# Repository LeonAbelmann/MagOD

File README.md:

# MagOD
Magnetic Optical Density meter
Tijmen Hageman, Jordi Hendrix, Hans Keizer, Marcel Welleweerd, Dave
van As, Ruthvik Bandaru, Rob Krawinkel, Leon Abelmann.

KIST Europe, University of Twente

## Other sources
Next to software, also the source codes to create hardware are
available here, as well as :

- Measurement head design, 3D print file (OpenSCAD, on [Thingiverse](https://www.thingiverse.com/thing:3122930) )
- Spice simulations, electronic diagrams, PCB layout (Spice, KiCad on
  [Dropbox](https://www.dropbox.com/sh/1dcai82byvd3hy0/AAA3AGXw0jbr9n2gzdcszufia))
- Laser cut pattern for housing electronics (DXF, on [Dropbox](https://www.dropbox.com/sh/1dcai82byvd3hy0/AAA3AGXw0jbr9n2gzdcszufia))

## Specifications
- Up to 800 samples per second, allows precise analysis of the rotation speed of magnetic bacteria
- Three-dimensional quasi-Helmholtz configuration, with fields up to 5 mT 
- Three color LED: red: 645 nm, 1000 mcd, green: 520 nm, 1700 mcd and blue 460 nm, 500 mcd
- Power supply with current feedback to compensate for coil heating, cut-off frequency 200 Hz
- Large area photodiode (sensitivity 0.5 mlx, with green LED theoretical max OD range of 5.8)
- Integrated pre-amplifier, SNR 83 dB (max OD range 4.0).
- Dedicated 16-bit ADS1115 DA converter
- Integrated temperature sensor
- Reference light detector
- Scattered light detector
- Fully programmable (ESP32 using Arduino IDE), open source
- User friendly spreadsheet recipe definition (csv format), with software to validate correctness
- Data collection on SD card, accessible by ftp over Wifi

## Additional info
- Marcel Welleweerd *and colleagues* (2022) ["An open-source automated magnetic optical density meter for analysis of suspensions of magnetic cells and particles"](https://doi.org/10.1063/5.0098008) Review of Scientific Instruments Vol 93, Issue 9, 094101. The manuscript can be found on [ArXiv](https://arxiv.org/abs/2106.07466)
- Chapter 8 in [Thesis](https://research.utwente.nl/en/publications/observing-magnetic-objects-in-fluids) Tijmen Hageman.
- [Presentation](https://youtu.be/TwwIsPg0qnI) by Leon Abelmann at Intermag2021

## How to join
Send mail to Leon (l.abelmann@tudelft.nl) if you are interested, all skills are welcome.

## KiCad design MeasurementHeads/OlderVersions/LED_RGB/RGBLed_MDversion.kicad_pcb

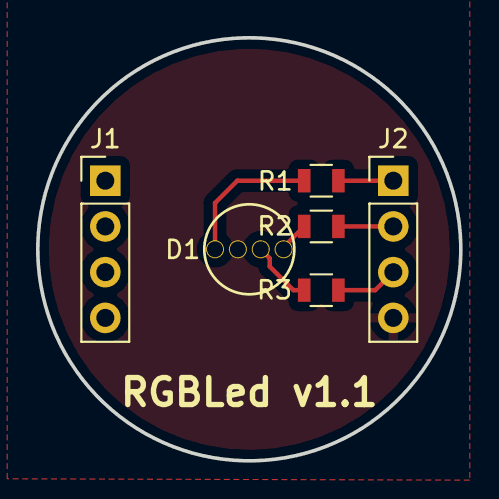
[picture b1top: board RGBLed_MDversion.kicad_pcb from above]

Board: 2 copper layers, 23.5 x 23.5 mm, 6 parts (0 on the bottom side), 7 nets.

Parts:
D1: LED_RABG; L-154A4SUREQBFZGEW
J1, J2: Conn_01x04; Socket_Strip_Straight_1x04_Pitch2.54mm
R1, R2, R3: R; R_0805

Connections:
+5V: D1.2, J2.4
/B: J2.3, R3.2
/G: J2.2, R2.2
/R: J2.1, R1.2
unnamed: D1.1, R1.1
unnamed: D1.3, R3.1
unnamed: D1.4, R2.1

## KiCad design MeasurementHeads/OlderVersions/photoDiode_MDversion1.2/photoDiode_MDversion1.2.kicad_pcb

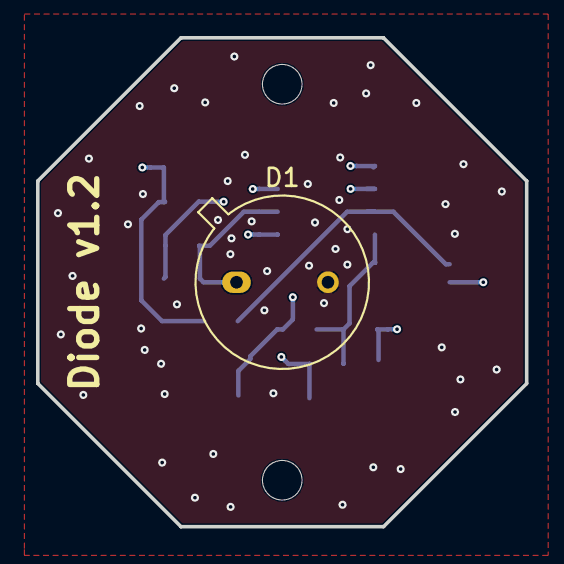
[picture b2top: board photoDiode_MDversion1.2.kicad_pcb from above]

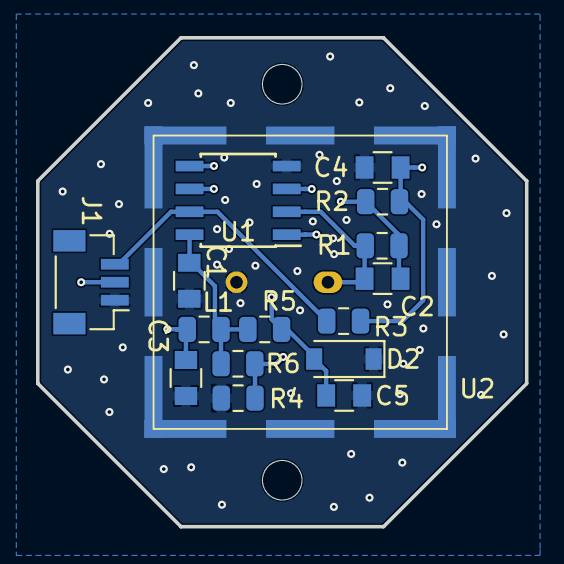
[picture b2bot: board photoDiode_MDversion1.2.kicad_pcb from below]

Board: 4 copper layers, 27.2 x 27.2 mm, 17 parts (16 on the bottom side), 9 nets.

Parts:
C1: 0.1uF; C_0805
C2, C5: C; C_0805
C3: 1.5uF; C_0805
C4: 47uF; C_0805
D1: BPW21; TO-5-2_Window
D2: D; D_SOD-123
J1: Conn_01x03; Molex_Pico-Clasp_501331-0307_1x03-1MP_P1.00mm_Vertical
L1: Ferrite_Bead; L_0805_2012Metric
R1, R3, R4, R5, R6: R; R_0805_2012Metric
R2: 3; R_0805_2012Metric
U1: Opamp_Dual_Generic; SOIC-8_3.9x4.9mm_Pitch1.27mm
U2: EMIshield; Laird-BMI-S-202-F

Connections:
+5V: C3.2, J1.2, L1.1
/A: J1.3, R3.2, U1.7
/Vdd: C1.1, L1.2, R5.2, R6.2, U1.8
GND: C1.2, C3.1, C4.2, C5.2, D1.2, D2.1, J1.1, R4.1, U1.4, U2.1
unnamed: C2.1, R1.2, R2.1, U1.1
unnamed: C2.2, D1.1, R1.1, U1.2
unnamed: C4.1, R2.2, R3.1, U1.6
unnamed: C5.1, D2.2, R5.1, U1.3
unnamed: R4.2, R6.1, U1.5

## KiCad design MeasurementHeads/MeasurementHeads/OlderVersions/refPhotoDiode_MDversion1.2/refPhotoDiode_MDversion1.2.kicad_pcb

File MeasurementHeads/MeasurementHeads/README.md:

# Measurement head electronics
photoDiode : photodetector
refPhotoDiode: board to holde RBG led/LED-mono module and reference photodiode
RGBLed: RGB Led module
LED_mono: Monochrome led module

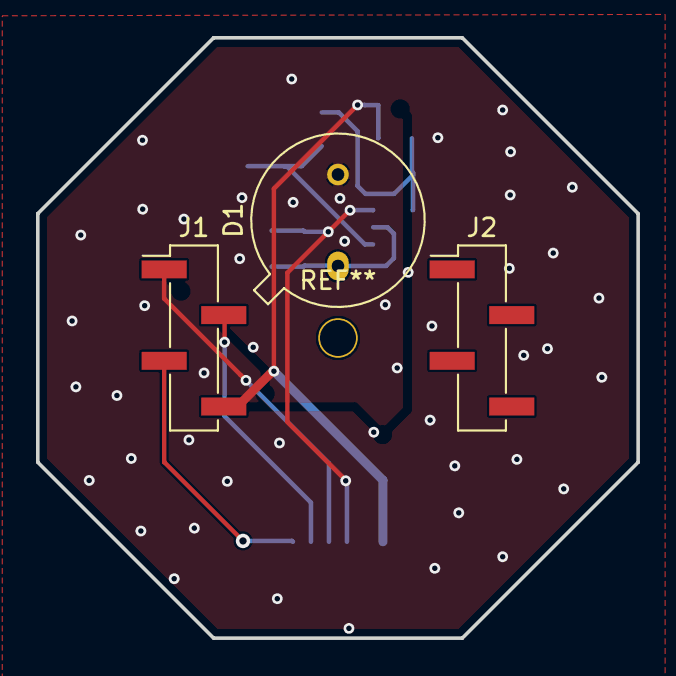
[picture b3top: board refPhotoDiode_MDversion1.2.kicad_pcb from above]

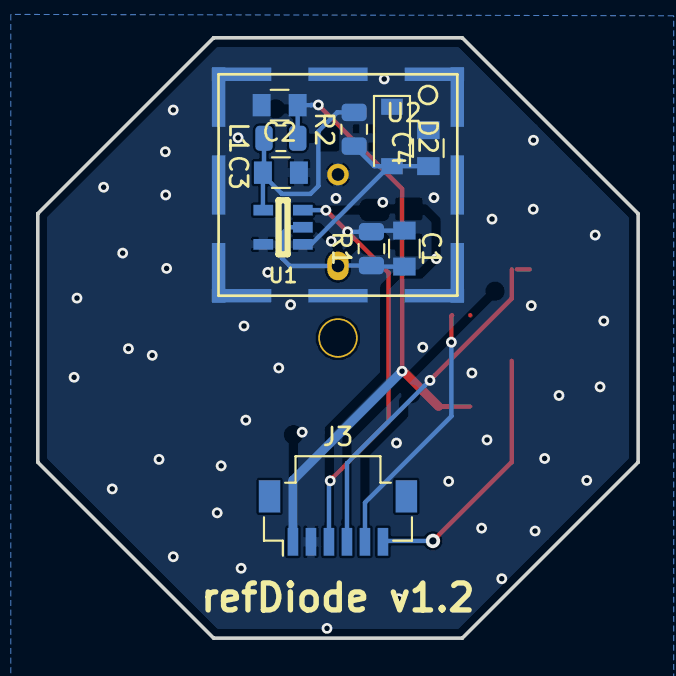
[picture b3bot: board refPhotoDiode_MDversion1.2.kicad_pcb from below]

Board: 2 copper layers, 33.4 x 33.4 mm, 14 parts (11 on the bottom side), 9 nets.

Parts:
C1, C4: C; C_0805
C2: 1.5uF; C_0805
C3: 0.1uF; C_0805
D1: BPW21; TO-5-2_Window
D2: D; D_SOD-123
J1, J2: Conn_01x04; PinHeader_1x04_P2.54mm_Vertical_SMD_Pin1Left
J3: Conn_01x06; Molex_Pico-Clasp_501331-0607_1x06-1MP_P1.00mm_Vertical
L1: Ferrite_Bead; L_0805_2012Metric
R1, R2: R; R_0805_2012Metric
U1: OPAMP; SOT-23-5
U2: EMIshield; Wurth-3610213126S-EMIshield-13.26x12.3mm

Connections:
+5V: C2.1, J1.4, J3.1, L1.1
/A: C1.1, J3.3, R1.2, U1.3
/B: J1.3, J3.6
/G: J1.2, J3.5
/R: J1.1, J3.4
/V: C3.1, L1.2, R2.2, U1.4
GND: C2.2, C3.2, C4.2, D1.2, D2.1, J3.2, U1.5, U2.1
unnamed: C1.2, D1.1, R1.1, U1.2
unnamed: C4.1, D2.2, R2.1, U1.1

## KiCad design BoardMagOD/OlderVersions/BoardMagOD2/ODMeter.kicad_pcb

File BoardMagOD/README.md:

# Measurement Board
Electronic design of measurement board

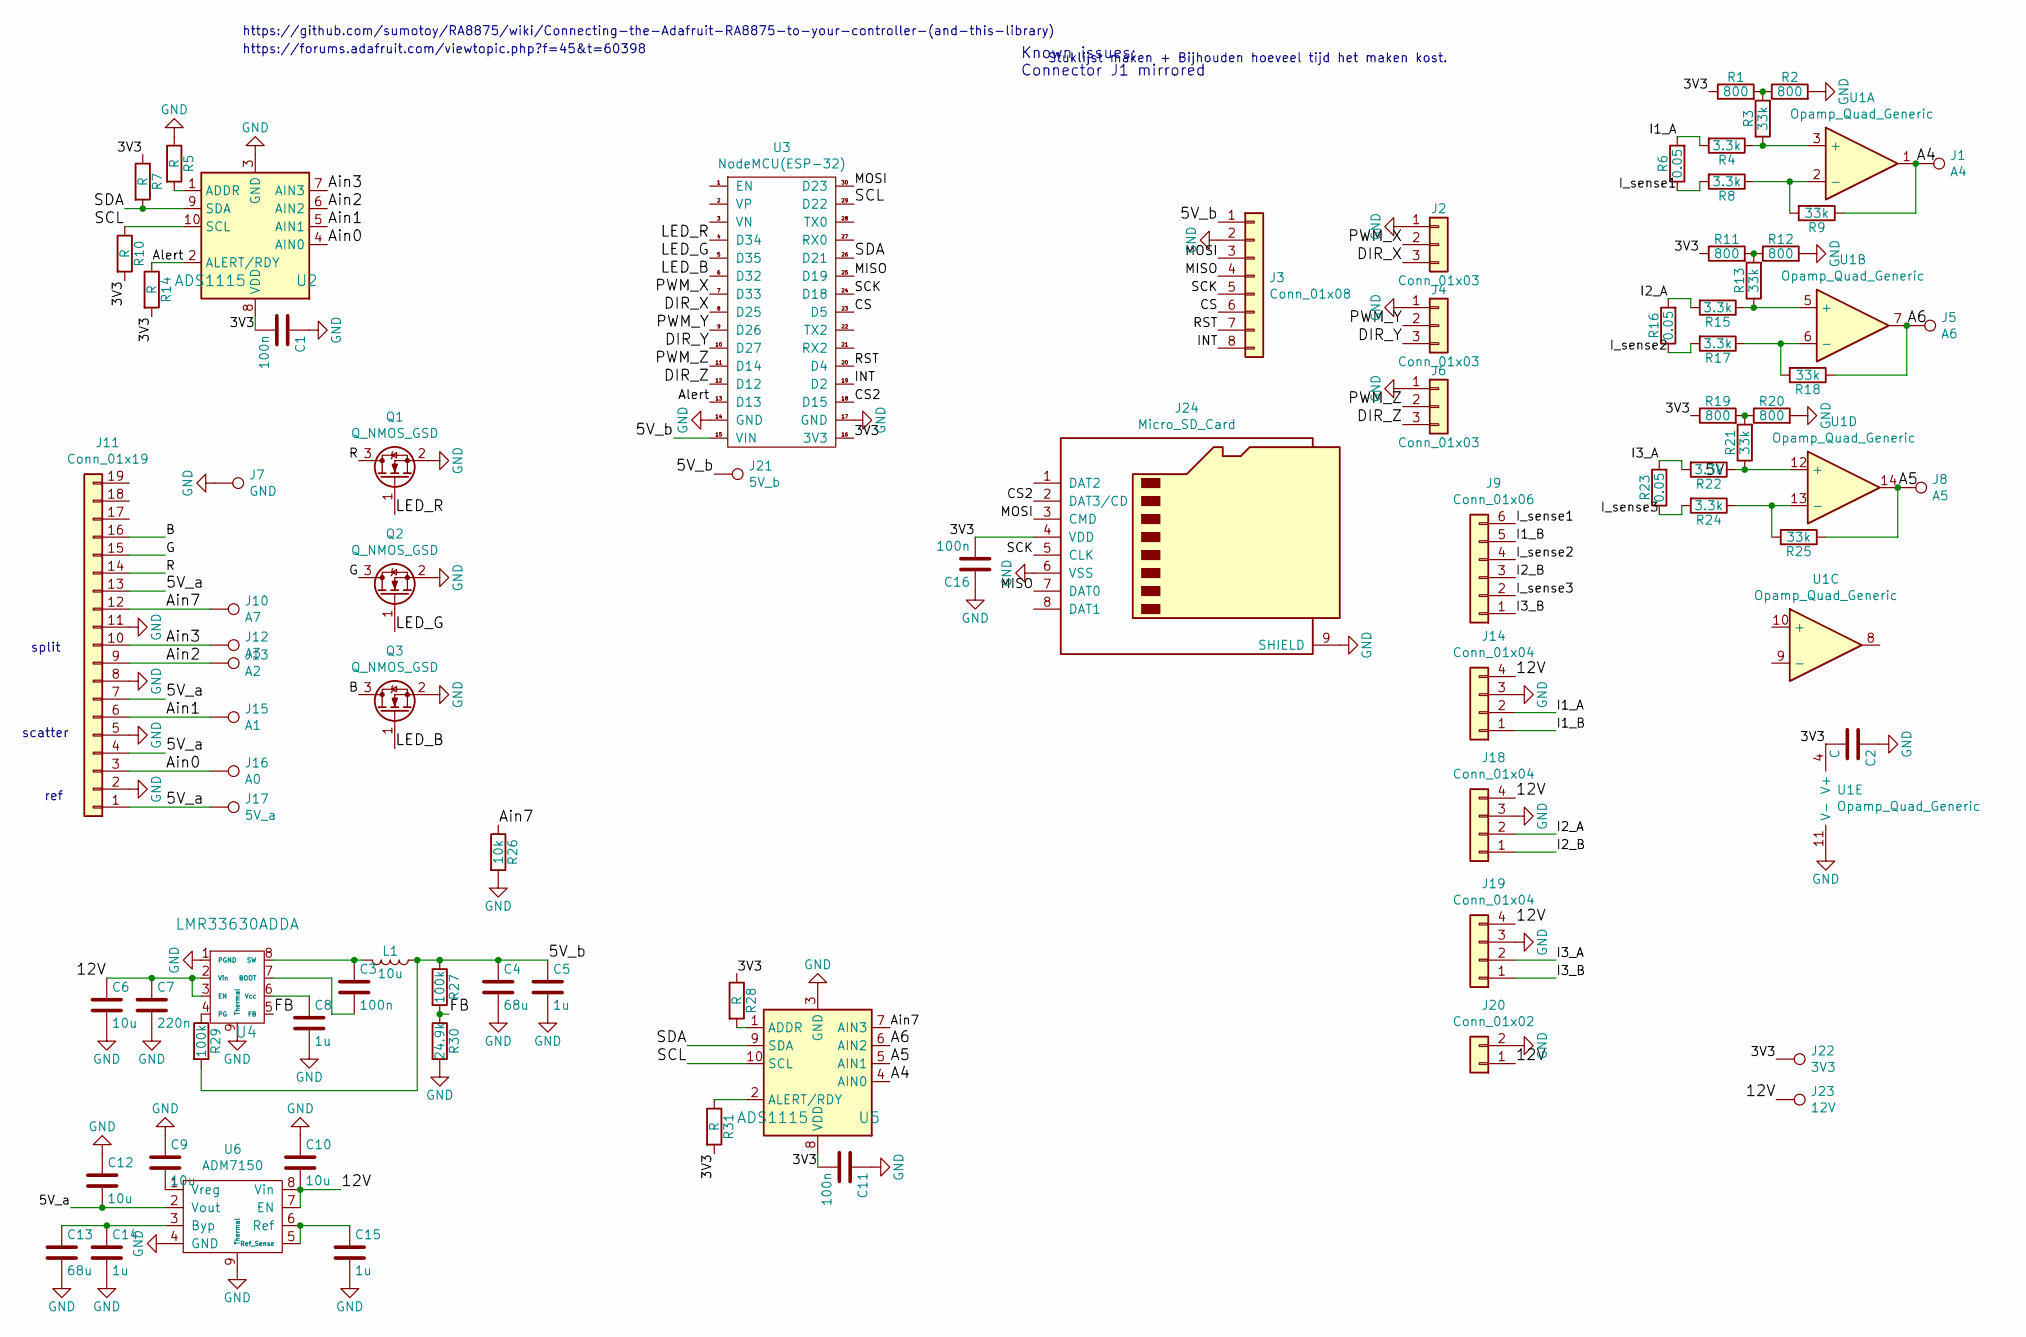
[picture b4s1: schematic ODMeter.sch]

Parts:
C1, C3, C11, C16: 100n; C_0805
C2: C; C_0805
C4, C13: 68u; CP_Tantalum_Case-D_EIA-7343-31_Hand
C5: 1u; C_0805
C6, C9, C10, C12: 10u; C_1210
C7: 220n; C_0805
C8, C14, C15: 1u; C_0603
J1: A4; TestPoint-Harwin-S2761-46R
J2, J4, J6: Conn_01x03; Pin_Header_Straight_1x03_Pitch2.54mm
J3: Conn_01x08; Pin_Header_Straight_1x08_Pitch2.54mm
J5: A6; TestPoint-Harwin-S2761-46R
J7: GND; TestPoint-Harwin-S2761-46R
J8: A5; TestPoint-Harwin-S2761-46R
J9: Conn_01x06; KK41791_straight1x6
J10: A7; TestPoint-Harwin-S2761-46R
J11: Conn_01x19; HDMI-RightAngle-47151-1051
J12: A3; TestPoint-Harwin-S2761-46R
J13: A2; TestPoint-Harwin-S2761-46R
J14, J18, J19: Conn_01x04; KK41791_straight1x4
J15: A1; TestPoint-Harwin-S2761-46R
J16: A0; TestPoint-Harwin-S2761-46R
J17: 5V_a; TestPoint-Harwin-S2761-46R
J20: Conn_01x02; KK396RPC171813_Straight_1x2
J21: 5V_b; TestPoint-Harwin-S2761-46R
J22: 3V3; TestPoint-Harwin-S2761-46R
J23: 12V; TestPoint-Harwin-S2761-46R
J24: Micro_SD_Card; MicroSd_Wurth_693072010801
L1: 10u; ssr1260
Q1, Q2, Q3: Q_NMOS_GSD; SOT-23
R1, R2, R11, R12, R19, R20: 800; R_0805
R3, R9, R13, R18, R21, R25: 33k; R_0805
R4, R8, R15, R17, R22, R24: 3.3k; R_0805
R5, R7, R10, R14, R28, R31: R; R_0805
R6, R16, R23: 0.05; OAR3
R26: 10k; R_0805
R27, R29: 100k; R_0805
R30: 24.9k; R_0805
U1: Opamp_Quad_Generic; SOIC-14_3.9x8.7mm_P1.27mm
U2, U5: ADS1115; VSSOP-10_3.1x3.1mm_Pitch0.5mm
U3: NodeMCU(ESP-32)
U4: LMR33630ADDA; HSOIC-8
U6: ADM7150; HSOIC-8

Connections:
/3V3: C1.2, C2.2, C11.2, C16.2, J22.1, J24.4 (VDD), R1.1, R7.1, R10.2, R11.1, R14.2, R19.1, R28.1, R31.2, U1.4 (V+), U2.8 (VDD), U3.16 (3V3), U5.8 (VDD)
/5V_a: C12.2, J11.1, J11.4, J11.7, J11.13, J17.1, U6.2 (Vout)
/5V_b: C4.1, C5.1, J3.1, J21.1, L1.1, R27.1, R29.2, U3.15 (VIN)
/12V: C6.1, C7.1, C10.2, J14.4, J18.4, J19.4, J20.1, J23.1, U4.2 (Vin), U4.3 (EN), U6.7 (EN), U6.8 (Vin)
/A4: J1.1, R9.1, U1.1, U5.4 (AIN0)
/A5: J8.1, R25.1, U1.14, U5.5 (AIN1)
/A6: J5.1, R18.1, U1.7, U5.6 (AIN2)
/Ain0: J11.3, J16.1, U2.4 (AIN0)
/Ain1: J11.6, J15.1, U2.5 (AIN1)
/Ain2: J11.9, J13.1, U2.6 (AIN2)
/Ain3: J11.10, J12.1, U2.7 (AIN3)
/Ain7: J10.1, J11.12, R26.1, U5.7 (AIN3)
/Alert: R14.1, U2.2 (ALERT/RDY), U3.13 (D13)
/B: J11.16, Q3.3 (D)
/CS: J3.6, U3.23 (D5)
/CS2: J24.2 (DAT3/CD), U3.18 (D15)
/DIR_X: J2.3, U3.8 (D25)
/DIR_Y: J4.3, U3.10 (D27)
/DIR_Z: J6.3, U3.12 (D12)
/FB: R27.2, R30.1, U4.5 (FB)
/G: J11.15, Q2.3 (D)
/I1_A: J14.2, R4.2, R6.2
/I1_B: J9.5, J14.1
/I2_A: J18.2, R15.2, R16.2
/I2_B: J9.3, J18.1
/I3_A: J19.2, R22.2, R23.2
/I3_B: J9.1, J19.1
/INT: J3.8, U3.19 (D2)
/I_sense1: J9.6, R6.1, R8.2
/I_sense2: J9.4, R16.1, R17.2
/I_sense3: J9.2, R23.1, R24.2
/LED_B: Q3.1 (G), U3.6 (D32)
/LED_G: Q2.1 (G), U3.5 (D35)
/LED_R: Q1.1 (G), U3.4 (D34)
/MISO: J3.4, J24.7 (DAT0), U3.25 (D19)
/MOSI: J3.3, J24.3 (CMD), U3.30 (D23)
/PWM_X: J2.2, U3.7 (D33)
/PWM_Y: J4.2, U3.9 (D26)
/PWM_Z: J6.2, U3.11 (D14)
/R: J11.14, Q1.3 (D)
/RST: J3.7, U3.20 (D4)
/SCK: J3.5, J24.5 (CLK), U3.24 (D18)
/SCL: R10.1, U2.10 (SCL), U3.29 (D22), U5.10 (SCL)
/SDA: R7.2, U2.9 (SDA), U3.26 (D21), U5.9 (SDA)
GND: C1.1, C2.1, C4.2, C5.2, C6.2, C7.2, C8.2, C9.1, C10.1, C11.1, C12.1, C13.2, C14.2, C15.2, C16.1, J2.1, J3.2, J4.1, J6.1, J7.1, J11.2, J11.5, J11.8, J11.11, J14.3, J18.3, J19.3, J20.2, J24.6 (VSS), J24.9 (SHIELD), Q1.2 (S), Q2.2 (S), Q3.2 (S), R2.2, R5.1, R12.2, R20.2, R26.2, R30.2, U1.11 (V-), U2.3 (GND), U3.14 (GND), U3.17 (GND), U4.1 (PGND), U4.9 (Thermal), U5.3 (GND), U6.4 (GND), U6.9 (Thermal)
unnamed: C3.1, L1.2, U4.8 (SW)
unnamed: C3.2, U4.7 (BOOT)
unnamed: C8.1, U4.6 (Vcc)
unnamed: C9.2, U6.1 (Vreg)
unnamed: C13.1, C14.1, U6.3 (Byp)
unnamed: C15.1, U6.5 (Ref_Sense), U6.6 (Ref)
unnamed: R1.2, R2.1, R3.2
unnamed: R3.1, R4.1, U1.3 (+)
unnamed: R5.2, U2.1 (ADDR)
unnamed: R8.1, R9.2, U1.2 (-)
unnamed: R11.2, R12.1, R13.2
unnamed: R13.1, R15.1, U1.5 (+)
unnamed: R17.1, R18.2, U1.6 (-)
unnamed: R19.2, R20.1, R21.2
unnamed: R21.1, R22.1, U1.12 (+)
unnamed: R24.1, R25.2, U1.13 (-)
unnamed: R28.2, U5.1 (ADDR)
unnamed: R29.1, U4.4 (PG)
unnamed: R31.1, U5.2 (ALERT/RDY)

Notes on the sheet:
Stuklijst maken + Bijhouden hoeveel tijd het maken kost.
Known issues: Connector J1 mirrored
ref
scatter
split
https://github.com/sumotoy/RA8875/wiki/Connecting-the-Adafruit-RA8875-to-your-controller-(and-this-library)
https://forums.adafruit.com/viewtopic.php?f=45&t=60398

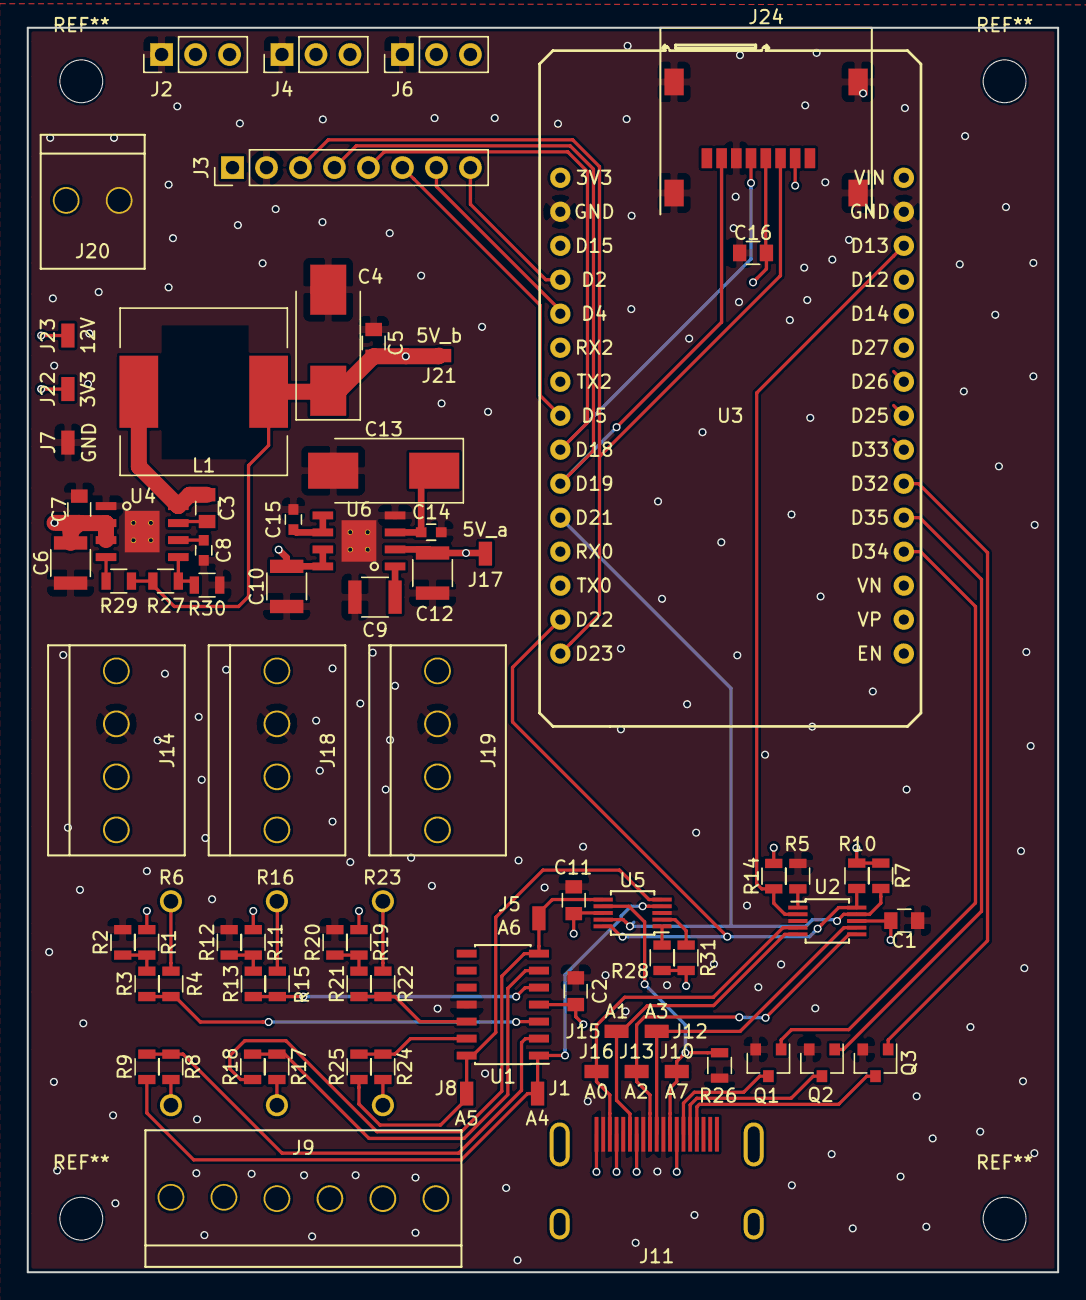
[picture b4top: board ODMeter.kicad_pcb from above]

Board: 4 copper layers, 77.0 x 93.0 mm, 81 parts (0 on the bottom side), 64 nets.

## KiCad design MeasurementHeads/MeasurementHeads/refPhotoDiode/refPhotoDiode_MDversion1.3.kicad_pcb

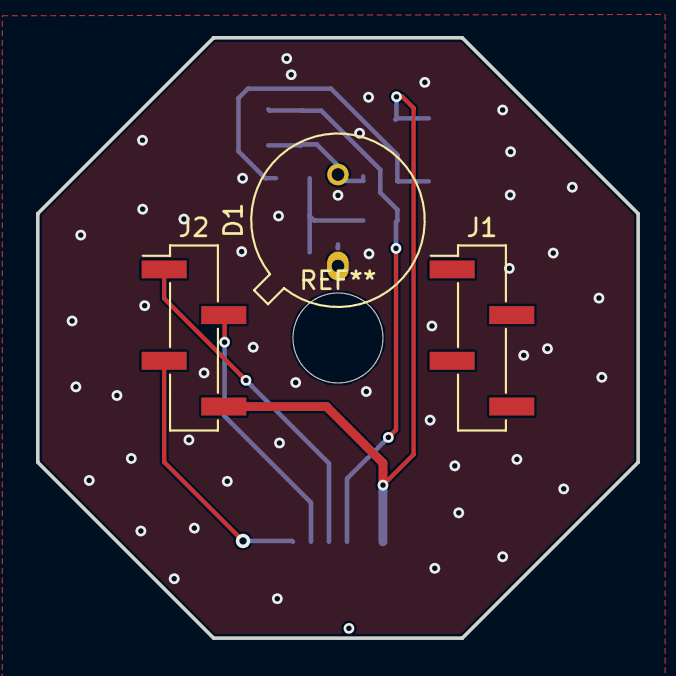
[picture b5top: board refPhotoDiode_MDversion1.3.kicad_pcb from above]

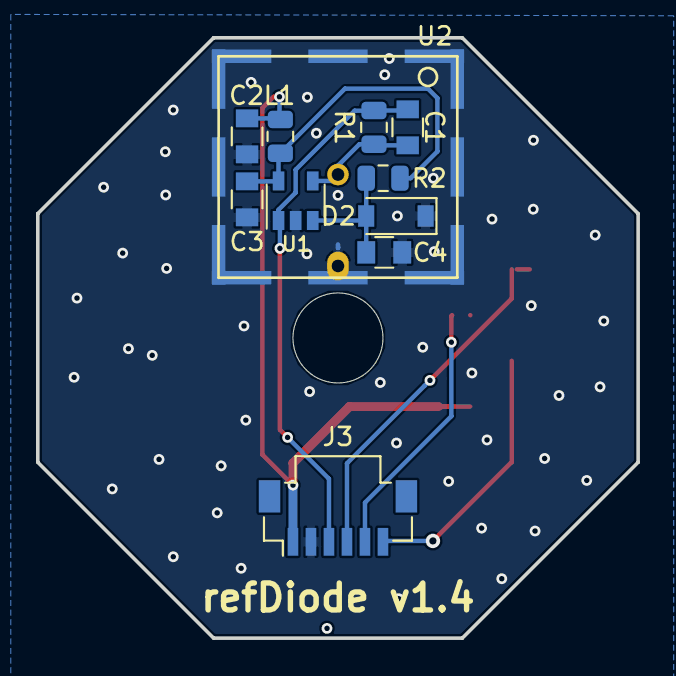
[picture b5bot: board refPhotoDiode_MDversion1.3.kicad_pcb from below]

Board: 2 copper layers, 33.4 x 33.4 mm, 14 parts (11 on the bottom side), 9 nets.

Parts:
C1: 180p; C_0805
C2: 1.5uF; C_0805
C3: 0.1uF; C_0805
C4: 1u; C_0805
D1: BPW21; TO-5-2_Window
D2: D; D_SOD-123
J1, J2: Conn_01x04; PinHeader_1x04_P2.54mm_Vertical_SMD_Pin1Left
J3: Conn_01x06; Molex_Pico-Clasp_501331-0607_1x06-1MP_P1.00mm_Vertical
L1: Ferrite_Bead; L_0805_2012Metric
R1: 1000k; R_0805_2012Metric
R2: 20k; R_0805_2012Metric
U1: OPA140; SOT-23-5
U2: EMIshield; Wurth-3610213126S-EMIshield-13.26x12.3mm

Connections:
+5V: C2.1, J2.4, J3.1, L1.1
/A: C1.1, J3.3, R1.2, U1.1
/B: J2.3, J3.6
/G: J2.2, J3.5
/R: J2.1, J3.4
/V: C3.1, L1.2, R2.2, U1.5
GND: C2.2, C3.2, C4.2, D1.2, D2.1, J3.2, U1.2, U2.1
unnamed: C1.2, D1.1, R1.1, U1.4
unnamed: C4.1, D2.2, R2.1, U1.3

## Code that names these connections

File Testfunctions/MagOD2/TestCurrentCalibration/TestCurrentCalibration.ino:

#include <SPI.h> // Communication
#include <Adafruit_GFX.h>    // Core graphics library
#include <Adafruit_ADS1015.h>  // ADC library

/* Help program that scans the PWM of the motordrivers and measures the current sensors adc4-6. If you connect a multimeter at the same time to the coils, you can make a graph of measured current versus real current */

/* TODO: There is a strange bug. Every time you change the channel, the adc outputs 19 or 20 for the first iteration. Only happens when the 12V is on and the coils are actuated.*/

#define RA8875_INT 16
#define RA8875_CS 5 
#define RA8875_RESET 17

/* MagOD2 has two ADS1115. 
   U2 with address pin to gnd, used for AIN0-3.
   U5 with address pin to VDD (3.3V), used for AIN4-7 */
#define ADS1015_ADDRESS_0 (0x48)// 1001 000 (ADDR -> GND)
#define ADS1015_ADDRESS_1 (0x49)// 1001 001 (ADDR -> VDD)
Adafruit_ADS1115 ads0(ADS1015_ADDRESS_0); //adc0-3;
Adafruit_ADS1115 ads1(ADS1015_ADDRESS_1); //adc4-7;

uint8_t Coil_x = 33; // pwm_x: output pin of the coils in the x direction
uint8_t Coil_y = 26; // pwm_y: output pin of the coils in the y direction
uint8_t Coil_z = 14; // pwm_z: output pin of the coils in the z direction
const uint32_t Frequency_PWM = 20000;    //set the pwm frequency of the coil-drivers
const int ledChannel_x = 3; /*0-15*/
const int ledChannel_y = 4; /*0-15*/
const int ledChannel_z = 5; /*0-15*/
const int resolution = 8; /* number bits resolution, 1-16 bit */
int Dir_x = 25;                /* direction pin of the coils in the x
				  direction low: output A of motor
				  driver is high and B is low
				  (positive direction), high: output A
				  of motor driver is low and B is high
				  (negative direction). See manual
				  MD13S page 6*/
int Dir_y = 27;                // direction pin of the coils in the y direction
int Dir_z = 12;                // direction pin of the coils in the z direction

/* help variable */

void setup () {
  Serial.begin(115200);

  /* Initialize the PWM */
 
 // Initialize channels 
  /*  channels 0-15, resolution 1-16 bits, freq limits depend on
       resolution ledcSetup(uint8_t channel, uint32_t freq, uint8_t
       resolution_bits);
     https://github.com/espressif/esp-idf/blob/master/docs/en/api-reference/peripherals/ledc.rst
  */

  ledcSetup(ledChannel_x, Frequency_PWM, resolution);
  ledcSetup(ledChannel_y, Frequency_PWM, resolution);
  ledcSetup(ledChannel_z, Frequency_PWM, resolution);

  ledcAttachPin(Coil_x, ledChannel_x);
  ledcAttachPin(Coil_y, ledChannel_y);
  ledcAttachPin(Coil_z, ledChannel_z);
    					
  /* Initialize the direction pins for the motor drives */
    /* sets the direction pin as output */
  pinMode(Dir_x, OUTPUT);
  pinMode(Dir_y, OUTPUT);
  pinMode(Dir_z, OUTPUT);
 

  /* Set the voltage */
  /* ledcWrite(channel, dutycycle)
     note that dutycycle ranges from 0-2^(resolution) set in ledcSetup
  2^11=2048*/
  ledcWrite(ledChannel_x, 0);
  ledcWrite(ledChannel_y, 0);
  ledcWrite(ledChannel_z, 0);

  /* Initialize ADC */
  ads0.setGain(GAIN_ONE);
  ads0.begin();
  ads1.setGain(GAIN_ONE);
  ads1.begin();
}

const int X=1;
const int Y=2;
const int Z=3;
int directions[]={Z}; //or {Y}, etc.
int num_dir=1;
// int directions[]={X,Y,Z}; 
// int num_dir=3;

void loop()
{
  int adc4, adc5, adc6, adc7; //Summed bit values of adc
  int ad4, ad5, ad6;//help variables for output adc

  int Dir_i = Dir_x;
  int Chan_i = ledChannel_x;

  Serial.println(directions[0]);
  
  for(int i = 0; i < num_dir; i = i + 1 )
    { 
      switch(directions[i]) {
      case X:
	Serial.println("X");
	Dir_i  = Dir_x;
	Chan_i = ledChannel_x;
	break;
      case Y:
	Serial.println("Y");
	Dir_i  = Dir_y;
	Chan_i = ledChannel_y;
	break;
      case Z:
	Serial.println("Z");
	Dir_i  = Dir_z;
	Chan_i = ledChannel_z;
	break;
      default:
	Serial.print("value not expected:");
	Serial.println(Dir_i);
      }
      
      for (double step = -1; step <= 1; step = step+0.2)
	{
	  /* Set the current direction */
	  if (step <  0) {digitalWrite(Dir_i, HIGH);};
	  if (step >= 0) {digitalWrite(Dir_i, LOW);};
	  /* Set the PWM, second value is relative to 2^resolution */
	  int PWM = fabs(step)*pow(2,resolution);//fabs is for doubles
	  ledcWrite(Chan_i, PWM);
	  delay(500);//wait for the system to settle

	  /* Read ADC1115 ports */
	  adc4 = 0;
	  adc5 = 0;
	  adc6 = 0;
	  int N = 150;
	  for (int j = 0; j < N; j++)
	    { ad4 = ads1.readADC_SingleEnded(0);
	      ad5 = ads1.readADC_SingleEnded(1);
	      ad6 = ads1.readADC_SingleEnded(2);
	      adc4 = adc4 + ad4;
	      adc5 = adc5 + ad5;
	      adc6 = adc6 + ad6;
	      // Serial.print(ad4);
	      // Serial.print(" ");
	      // Serial.print(ad5);
	      // Serial.print(" ");
	      // Serial.println(ad6);
	    }

	  if (step < 0)  {Serial.print("-");};
	  if (step >= 0) {Serial.print(" ");};
	  Serial.print(PWM);
	  Serial.print(", ");
	  Serial.print(adc4/N);
	  Serial.print(", ");
	  Serial.print(adc5/N);
	  Serial.print(", ");
	  Serial.println(adc6/N);
	}
      ledcWrite(Chan_i, 0); //Stop current
    }  
}

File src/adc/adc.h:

/* adc.h
 MagOD libary 
 December 2020
 Photodiode readout
 Tijmen Hageman, Jordi Hendrix, Hans Keizer, Leon Abelmann 
*/
#ifndef adc_h
#define adc_h

//#include <Adafruit_ADS1015.h>  // ADC library, now included in standard libraries
#include "../MagOD_ADS1115/MagOD_ADS1115.h" // Modified Adafruit_ADS1015 lib


#include "../../MagOD.h"
#include "../led/led.h" // Needed for set_vrefs. adc and led are interdepenent. Perhaps solve in MagOD itself. TODO. LEON

/* addresses of ADS1115 ADC's */
#define ADS1115_ADDRESS_0 (0x48) // 1001 000 (ADDR -> GND)
#define ADS1115_ADDRESS_1 (0x49) // 1001 001 (ADDR -> VDD)
/* ESP32 pin that the ready pin of the ADC is attached to */
#define ADS1115_RDY 13                     
/* samplerate for adc0 */
#define sampleRateADC0 0 /* Sample rates: 0: 8 SPS, 1: 16 SPS, 2: 32
			    SPS, 3: 64 SPS, 4: 128 SPS, 5: 250 SPS, 6:
			    475 SPS 7: 860 SPS */

#if defined(_MAGOD1)
#define Temp_read //12 //Pin for NTC ADC
#endif
/* MagOD2 uses adc1 for reading temperature */


/* Definition of the buffer size, how many elements does it have */
#define bufferSize 1000
/* Buffer data structure type*/
typedef struct {
  uint8_t ch;                 // Channel that was measured on
  uint16_t val;               // Value that was measured
  unsigned long time;         // Time of the measurement
  /* the millis function returns a 32bit value meaning it will
     overflow after 49 days */
} bufferData_t;

/* readable names for the ADC channels */
#define SCAT  0 /* ads0 ADC0 Ain0 scattering photodiode */
#define DIODE 1 /* ads0 ADC1 Ain1 photodetector */
#define SPLIT 2 /* ads0 ADC2 Ain2 not connected */
#define LED   3 /* ads0 ADC3 Ain3 photodiode that measures LED directly */
#define IX    4 /* ads1 ADC0 A4 x-coils current monitor */
#define IZ    5 /* ads1 ADC1 A5 y-coils current monitor */
#define IY    6 /* ads1 ADC1 A6 z-coils current monitor */
#define NTC   7 /* ads1 ADC3 Ain7 ADCNTC temperature sensor */
// MagOD1 has DIODE_UP ad 2 DIODE_DOWN at 3.


class adc
{
 public:
  adc();
  void       initADC(); /* Start the ADCs with correct amplification,etc */
  bool       bufferEmpty();//Check if ADC0 buffer has data
  dataPoint  getDataPoint(); /* Get datapoint and convert*/

  /* void       set_vrefs(references &Vref, bool ref_all_wavelength, led myled);  */
  /* diodes     readDiodes(); // Read the signals from the photodiodes */
  /* double     readTemp(); //Read the temperature sensor */
  /* feedbacks  readFeedbacks();//Read the currents to the coils */
 private:
};

#endif

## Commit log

2019-01-13 Version that compiles and runs on Arduino Mega 2560 with 1.8" screen. Not tested on real MagOD
2019-01-13 moved globals to MagOD.h
2019-01-14 removed Testfunctions from repository
2019-01-23 tested on hardware, corrected errors in array intialization. Correct wrong threshold in button_left. Cosmetics here and there.
2019-04-07 added testfiles
2019-04-07 removed directory that should not be here
2019-04-07 removed directories from repository that were not fit for publishing yet
2019-04-07 added .gitignore to repo
2019-04-07 added README.md
2019-04-07 removed directories that are not ready to publish yet
2019-04-07 deleted arduino dir
2019-04-07 new files, confused now...
2019-04-07 changed README.md files
2019-04-07 removed TestTFT50 directory ,contains material that should not be publishe
2019-05-09 MagOD1 compiling and running Added Matlab code for analysis of datafiles
2019-07-06 Version for MagOD2 improved
2019-07-06 updated for MagOD hardware
2019-07-06 removed unnecessary pins.h
2019-08-26 new testfunctions
2019-08-26 update after testing new MagOD2
2019-09-18 made testarea for new recipes function
2019-09-18 redefined defintions, didn't work. added example
2019-09-19 added file read example
2019-09-21 changed file format
2019-09-26 made new examples
2019-10-17 Defined the array of recipes
2020-01-28 updated files
2020-02-15 Adjustable LED intensity during program. Test function for LED Test function for TFT screen
2020-03-18 Introduced ReadRecipes: read RECIPES.CSV from Flash card. First only test to check if recipe is read well.
2020-03-21 Try to test recipes reading on computer, rather than ESP32
2020-04-01 C++ file for testing the Recipes
2020-04-03 TestRecipes, split of the command line and Arduino versions in an organised way
2020-04-03 added TestRecipes.cpp (link)
2020-04-03 new recipes.csv
2020-04-04 fixed error with (char *)
2020-04-06 fixed makefile
2020-04-08 initialized file variable and file functions
2020-04-08 removed unnecessary files
2020-04-14 update with interupt based readout
2020-04-14 libray for interupt based readout
2020-04-17 SD card test
2020-05-20 new SD HTTP server test script
2020-05-27 Select samplerate ADC Recipes are read from csv file, recipes.* compatible with command line version
2020-05-27 Adapted MagOD.* for new recipes routines New testing routines
2020-05-27 removed binaries
2020-05-27 removed ReadSerial
2020-05-27 added directories to ignore
2020-05-27 removed testfunction
2020-05-27 removed testfunctions that should not be on repository
2020-05-30 moved password to separate (hidden) file. Adapted SD card access.
2020-05-31 Added display and selection of recipes. Adapted recipes.cpp of Ruthvik to MagOD environment. Fixed bug with first recipe step being skipped.
2020-05-31 Tweaks on screen layout. Added example RECIPES.CSV
2020-06-07 Corrected error in field calibration. Tweaked screen layout.
2020-07-10 Nasty bug in z-field, lost attachment to channel
2020-07-10 removed negative value correction
    from line 163 to 171
2020-08-14 fixed indentation to improve readability
2020-08-14 Added a new test implementing a queue after ADC0
2020-08-17 still some open files. not sure if commit is a good idea :(
2020-08-20 Added more comments to clarify the working of the queue test
2020-10-15 Modifications preparing for the Bayreuth system. Introduced calibration.h for all system dependent settings. Fixed error with Vref setting. Also switched on the led immediately after loading recipe.
2020-12-28 implemented ADC buffer, two cores, Wifi and ftp server
2021-01-03 Added NTP (time/date) support for timestamps of files on SD card, and file info for FTP client
2021-01-06 improved filename represenation
2021-01-06 improved README
2021-01-06 improved links in README
2021-01-06 fixed typo
2021-01-09 fixed Nr_cycles bug
2021-01-10 worked on graph, moved to new macbook
2021-01-17 autoscale graph and time info
2021-01-28 Max sequence error corrected, copy previous measurement in brown, changed some non necessary unsigned int to simple int
2021-02-14 fixed error for number of recipes sequences > 15. Experiments with python reading of data files
2021-02-14 corrected for missing parameters CEA/Bayreuth
2021-06-11 added license
2021-06-21 confusing
2021-09-01 fixed error in calculation OD on screen
2021-09-28 Implement autoCmag recipe, which calculates OD and Cmag automatically and displays on the touchscreen
2021-10-14 corrected version number
2021-10-24 Added screen reset. Code cleanup.
2022-07-05 Copied from Dropbox
2022-07-05 indicated files now also on github
2022-07-05 correct incorrect directory structure
